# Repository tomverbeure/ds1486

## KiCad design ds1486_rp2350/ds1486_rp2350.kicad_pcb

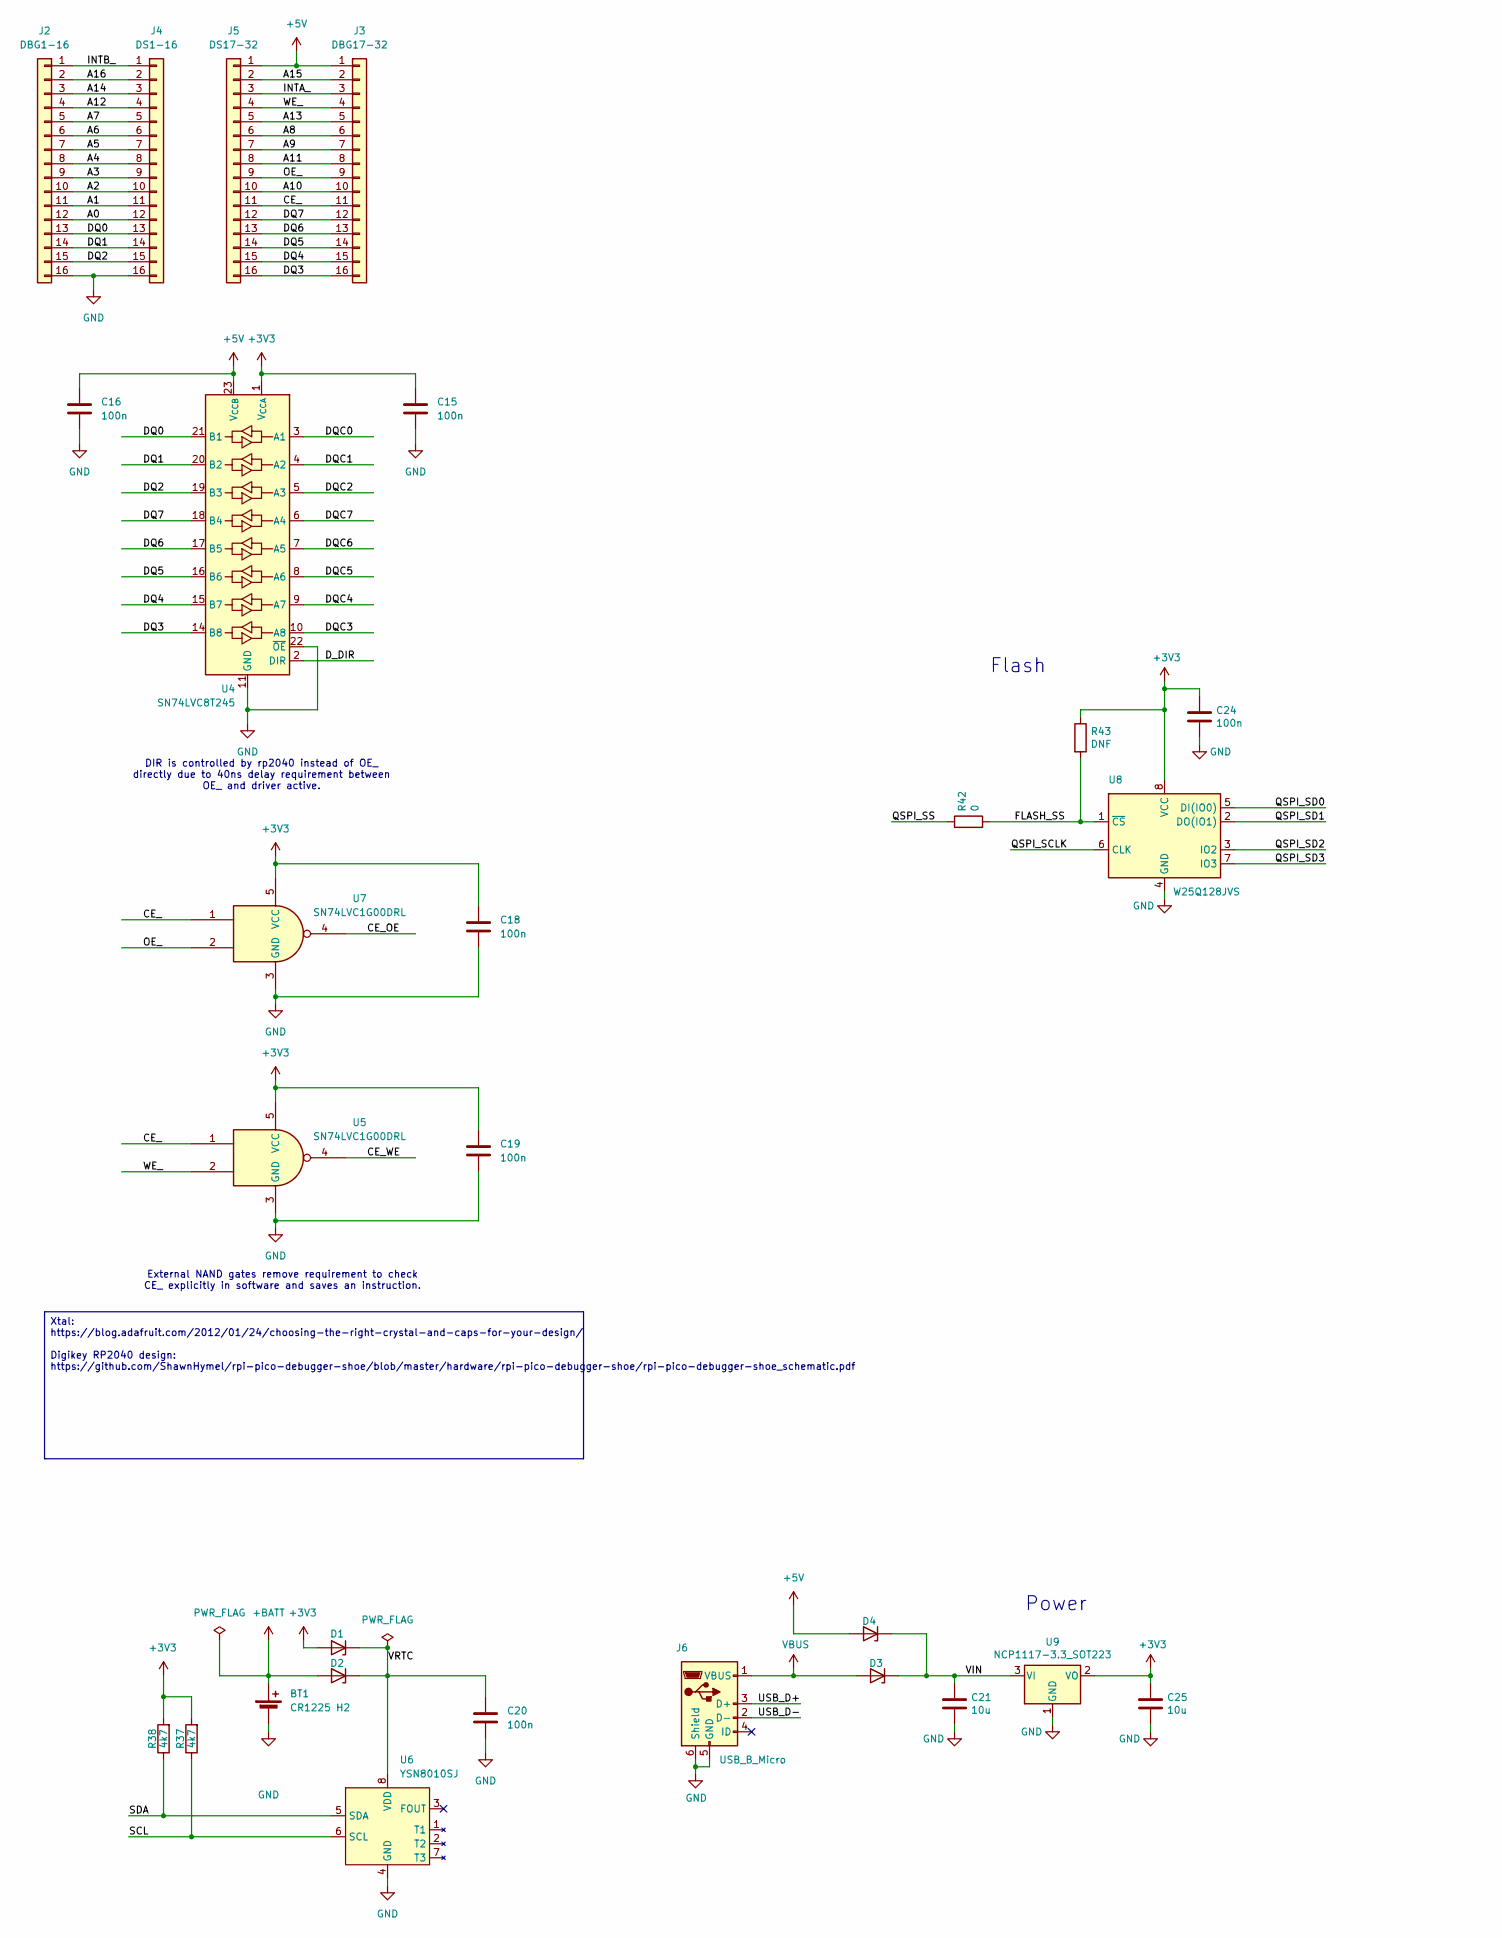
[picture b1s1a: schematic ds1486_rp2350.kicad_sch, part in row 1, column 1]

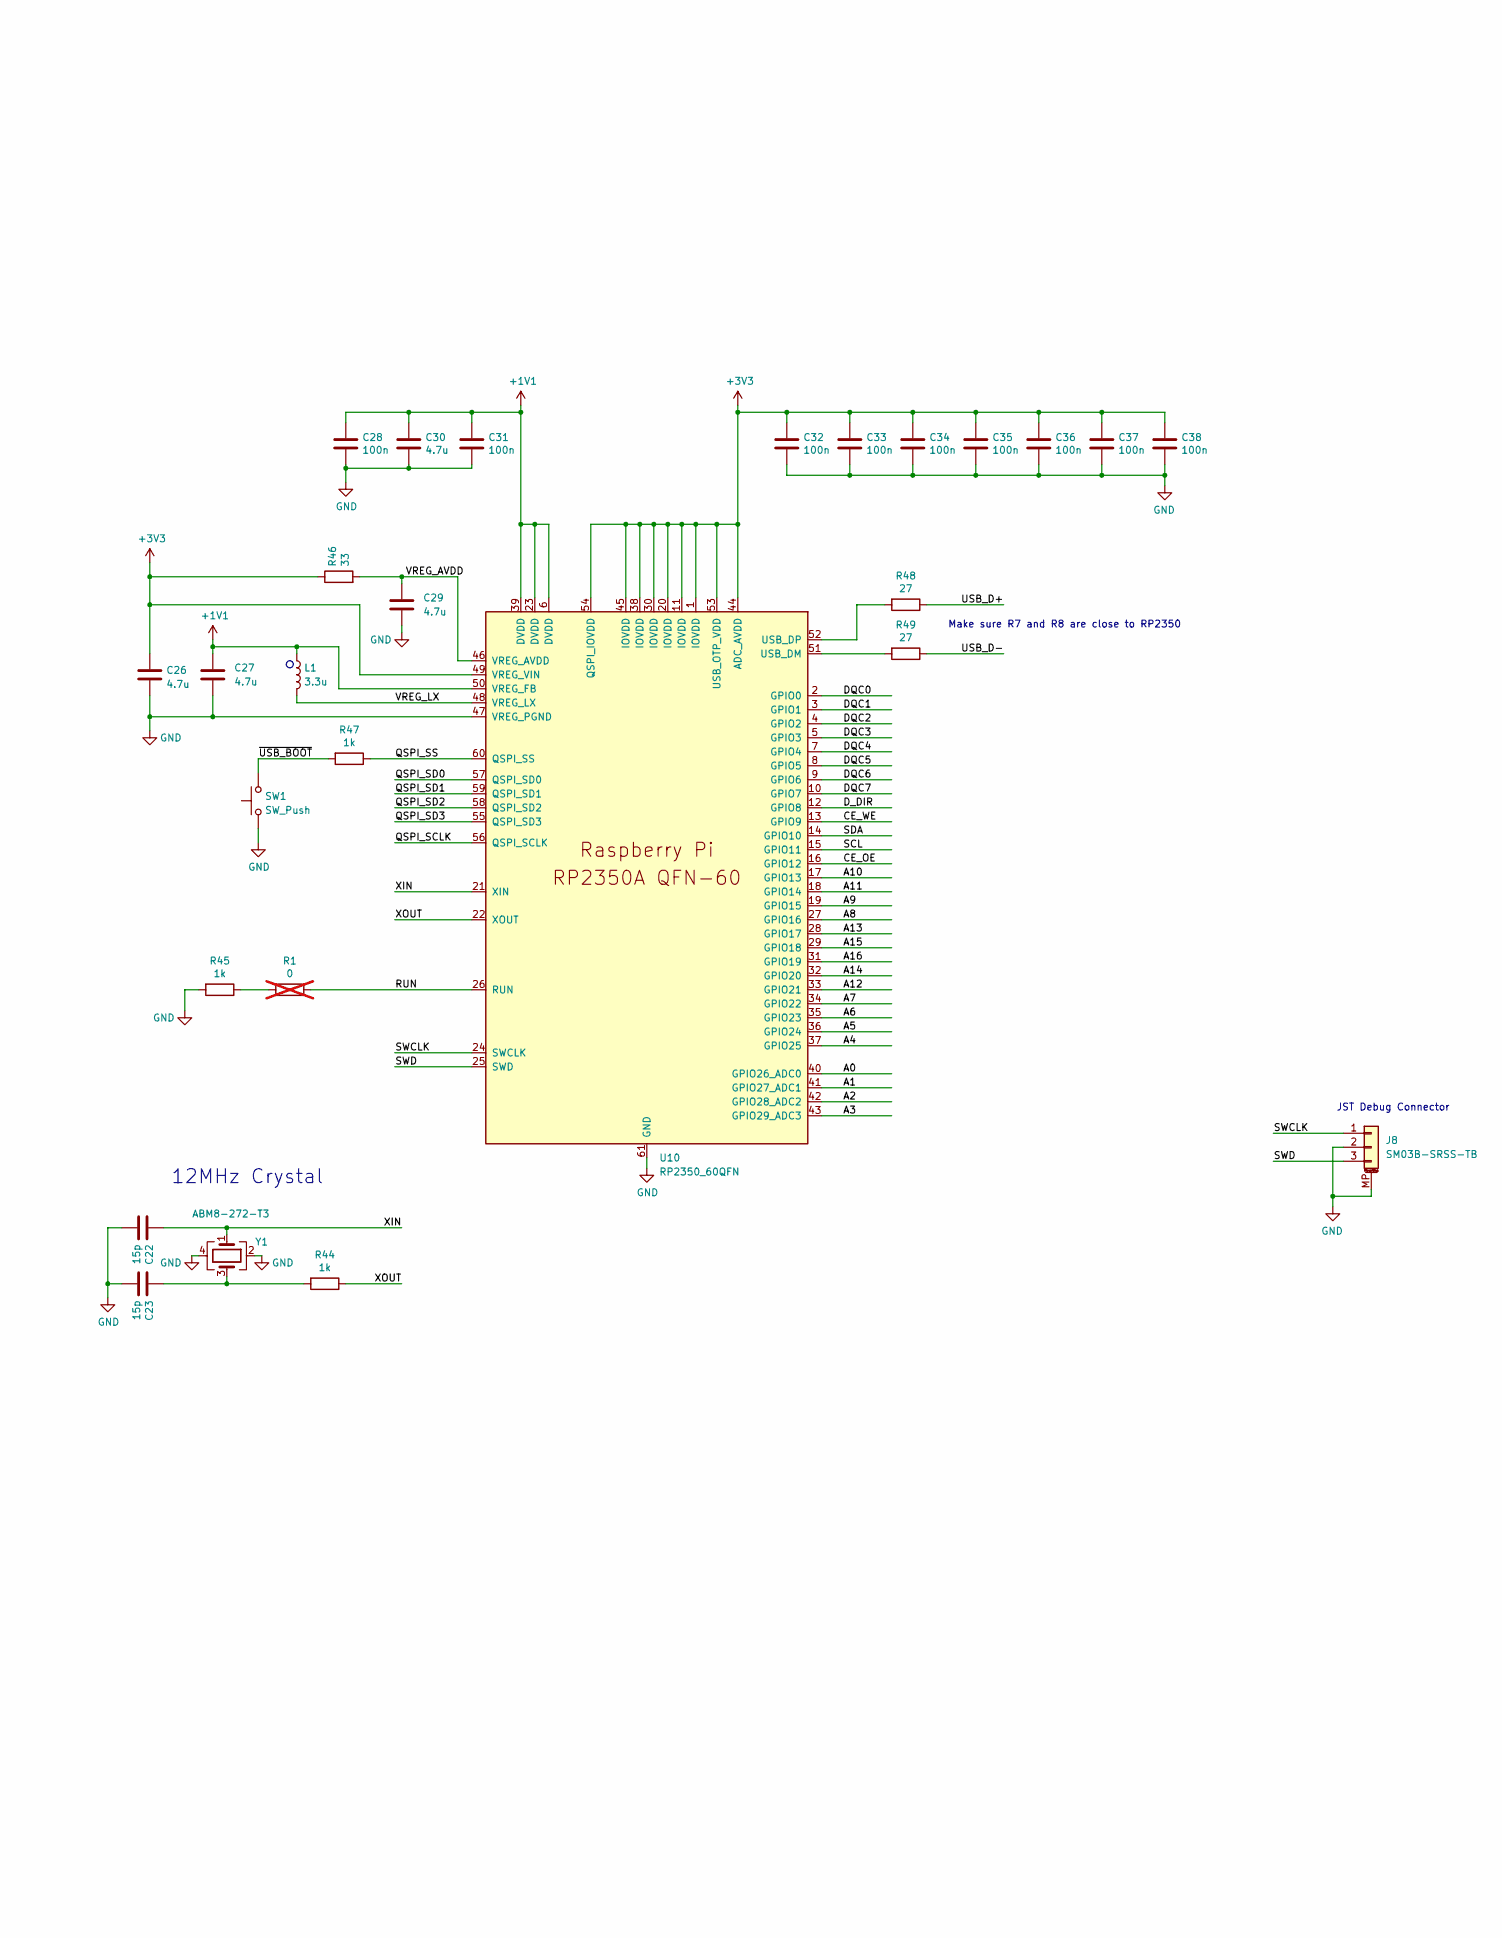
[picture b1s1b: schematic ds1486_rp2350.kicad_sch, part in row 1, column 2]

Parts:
BT1: CR1225 H2; CR1225_H2
C15, C16, C20: 100n; C_0603_1608Metric
C18, C19, C24, C28, C31, C32, C33, C34, C35, C36, C37, C38: 100n; C_0402_1005Metric
C21, C25: 10u; C_0805_2012Metric
C22, C23: 15p; C_0402_1005Metric
C26, C27: 4.7u; C_0402_1005Metric_small_pads
C29, C30: 4.7u; C_0402_1005Metric
D1, D2, D3, D4: BZT52C6V8-7-F; D_SOD-123F
J2: DBG1-16; PinHeader_1x16_P2.54mm_Vertical
J3: DBG17-32; PinHeader_1x16_P2.54mm_Vertical
J4: DS1-16; PinHeader_1x16_P2.54mm_Vertical_DIP_Diameter_Flipside
J5: DS17-32; PinHeader_1x16_P2.54mm_Vertical_DIP_Diameter_Flipside
J6: USB_B_Micro; USB_Micro-B_Amphenol_10103594-0001LF_Horizontal
J8: SM03B-SRSS-TB; JST_SH_SM03B-SRSS-TB_1x03-1MP_P1.00mm_Horizontal
L1: 3.3u; L_pol_2016
R1: 0; R_0402_1005Metric; not fitted
R37, R38: 4k7; R_0402_1005Metric
R42: 0; R_0402_1005Metric
R43: DNF; R_0402_1005Metric
R44, R45, R47: 1k; R_0402_1005Metric
R46: 33; R_0402_1005Metric
R48, R49: 27; R_0402_1005Metric
SW1: SW_Push; SW_Push_1P1T_NO_Vertical_Wuerth_434133025816
U4: SN74LVC8T245; SSOP-24_3.9x8.7mm_P0.635mm
U5, U7: SN74LVC1G00DRL; Texas_R-PDSO-N5_DRL-5
U6: YSN8010SJ; SOP-8_3.9x4.9mm_P1.27mm
U8: W25Q128JVS; SOIC-8_5.23x5.23mm_P1.27mm
U9: NCP1117-3.3_SOT223; SOT-223-3_TabPin2
U10: RP2350_60QFN; QFN-60-1EP_7x7mm_P0.4mm_EP3.4x3.4mm
Y1: ABM8-272-T3; Crystal_SMD_3225-4Pin_3.2x2.5mm

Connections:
+1V1: C27.1, C28.1, C30.1, C31.1, L1.1, U10.6 (DVDD), U10.23 (DVDD), U10.39 (DVDD), U10.50 (VREG_FB)
+3V3: C15.1, C18.1, C19.1, C24.1, C25.1, C26.1, C32.1, C33.1, C34.1, C35.1, C36.1, C37.1, C38.1, D1.2 (A), R37.2, R38.2, R43.1, R46.1, U4.1 (V_{CCA}), U5.5 (VCC), U7.5 (VCC), U8.8 (VCC), U9.2 (VO), U10.1 (IOVDD), U10.11 (IOVDD), U10.20 (IOVDD), U10.30 (IOVDD), U10.38 (IOVDD), U10.44 (ADC_AVDD), U10.45 (IOVDD), U10.49 (VREG_VIN), U10.53 (USB_OTP_VDD), U10.54 (QSPI_IOVDD)
+5V: C16.1, D4.2 (A), J3.1, J5.1, U4.23 (V_{CCB}), U4.24 (V_{CCB})
+BATT: BT1.1 (+), D2.2 (A)
/A0: J2.12, J4.12, U10.40 (GPIO26_ADC0)
/A1: J2.11, J4.11, U10.41 (GPIO27_ADC1)
/A2: J2.10, J4.10, U10.42 (GPIO28_ADC2)
/A3: J2.9, J4.9, U10.43 (GPIO29_ADC3)
/A4: J2.8, J4.8, U10.37 (GPIO25)
/A5: J2.7, J4.7, U10.36 (GPIO24)
/A6: J2.6, J4.6, U10.35 (GPIO23)
/A7: J2.5, J4.5, U10.34 (GPIO22)
/A8: J3.6, J5.6, U10.27 (GPIO16)
/A9: J3.7, J5.7, U10.19 (GPIO15)
/A10: J3.10, J5.10, U10.17 (GPIO13)
/A11: J3.8, J5.8, U10.18 (GPIO14)
/A12: J2.4, J4.4, U10.33 (GPIO21)
/A13: J3.5, J5.5, U10.28 (GPIO17)
/A14: J2.3, J4.3, U10.32 (GPIO20)
/A15: J3.2, J5.2, U10.29 (GPIO18)
/A16: J2.2, J4.2, U10.31 (GPIO19)
/CE_: J3.11, J5.11, U5.1, U7.1
/CE_OE: U7.4, U10.16 (GPIO12)
/CE_WE: U5.4, U10.13 (GPIO9)
/DQ0: J2.13, J4.13, U4.21 (B1)
/DQ1: J2.14, J4.14, U4.20 (B2)
/DQ2: J2.15, J4.15, U4.19 (B3)
/DQ3: J3.16, J5.16, U4.14 (B8)
/DQ4: J3.15, J5.15, U4.15 (B7)
/DQ5: J3.14, J5.14, U4.16 (B6)
/DQ6: J3.13, J5.13, U4.17 (B5)
/DQ7: J3.12, J5.12, U4.18 (B4)
/DQC0: U4.3 (A1), U10.2 (GPIO0)
/DQC1: U4.4 (A2), U10.3 (GPIO1)
/DQC2: U4.5 (A3), U10.4 (GPIO2)
/DQC3: U4.10 (A8), U10.5 (GPIO3)
/DQC4: U4.9 (A7), U10.7 (GPIO4)
/DQC5: U4.8 (A6), U10.8 (GPIO5)
/DQC6: U4.7 (A5), U10.9 (GPIO6)
/DQC7: U4.6 (A4), U10.10 (GPIO7)
/D_DIR: U4.2 (DIR), U10.12 (GPIO8)
/FLASH_SS: R42.2, R43.2, U8.1 (~CS)
/INTA_: J3.3, J5.3
/INTB_: J2.1, J4.1
/OE_: J3.9, J5.9, U7.2
/QSPI_SCLK: U8.6 (CLK), U10.56 (QSPI_SCLK)
/QSPI_SD0: U8.5 (DI(IO0)), U10.57 (QSPI_SD0)
/QSPI_SD1: U8.2 (DO(IO1)), U10.59 (QSPI_SD1)
/QSPI_SD2: U8.3 (IO2), U10.58 (QSPI_SD2)
/QSPI_SD3: U8.7 (IO3), U10.55 (QSPI_SD3)
/QSPI_SS: R42.1, R47.1, U10.60 (QSPI_SS)
/RUN: R1.1, U10.26 (RUN)
/SCL: R37.1, U6.6 (SCL), U10.15 (GPIO11)
/SDA: R38.1, U6.5 (SDA), U10.14 (GPIO10)
/SWCLK: J8.1, U10.24 (SWCLK)
/SWD: J8.3, U10.25 (SWD)
/USB_D+: J6.3 (D+), R48.1
/USB_D-: J6.2 (D-), R49.1
/VIN: C21.1, D3.1 (K), D4.1 (K), U9.3 (VI)
/VREG_AVDD: C29.1, R46.2, U10.46 (VREG_AVDD)
/VREG_LX: L1.2, U10.48 (VREG_LX)
/VRTC: C20.1, D1.1 (K), D2.1 (K), U6.8 (VDD)
/WE_: J3.4, J5.4, U5.2
/XIN: C22.1, U10.21 (XIN), Y1.1
/XOUT: R44.1, U10.22 (XOUT)
/~USB_BOOT: R47.2, SW1.2
GND: BT1.2 (-), C15.2, C16.2, C18.2, C19.2, C20.2, C21.2, C22.2, C23.2, C24.2, C25.2, C26.2, C27.2, C28.2, C29.2, C30.2, C31.2, C32.2, C33.2, C34.2, C35.2, C36.2, C37.2, C38.2, J2.16, J4.16, J6.5 (GND), J6.6 (Shield), J8.2, J8.MP (MountPin), R45.2, SW1.1, U4.11 (GND), U4.12 (GND), U4.13 (GND), U4.22 (~OE), U5.3 (GND), U6.4 (GND), U7.3 (GND), U8.4 (GND), U9.1 (GND), U10.47 (VREG_PGND), U10.61 (GND), Y1.2, Y1.4
unnamed: C23.1, R44.2, Y1.3
unnamed: R1.2, R45.1
unnamed: R49.2, U10.51 (USB_DM)
unnamed: R48.2, U10.52 (USB_DP)
VBUS: D3.2 (A), J6.1 (VBUS)

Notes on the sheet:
Flash
DIR is controlled by rp2040 instead of OE_ directly due to 40ns delay requirement between OE_ and driver active.
External NAND gates remove requirement to check CE_ explicitly in software and saves an instruction.
12MHz Crystal
Make sure R7 and R8 are close to RP2350
Power
JST Debug Connector
Xtal: https://blog.adafruit.com/2012/01/24/choosing-the-right-crystal-and-caps-for-your-design/ Digikey RP2040 design: https://github.com/ShawnHymel/rpi-pico-debugger-shoe/blob/master/hardware/rpi-pico-debugger-shoe/rpi-pico-debugger-shoe_schematic.pdf

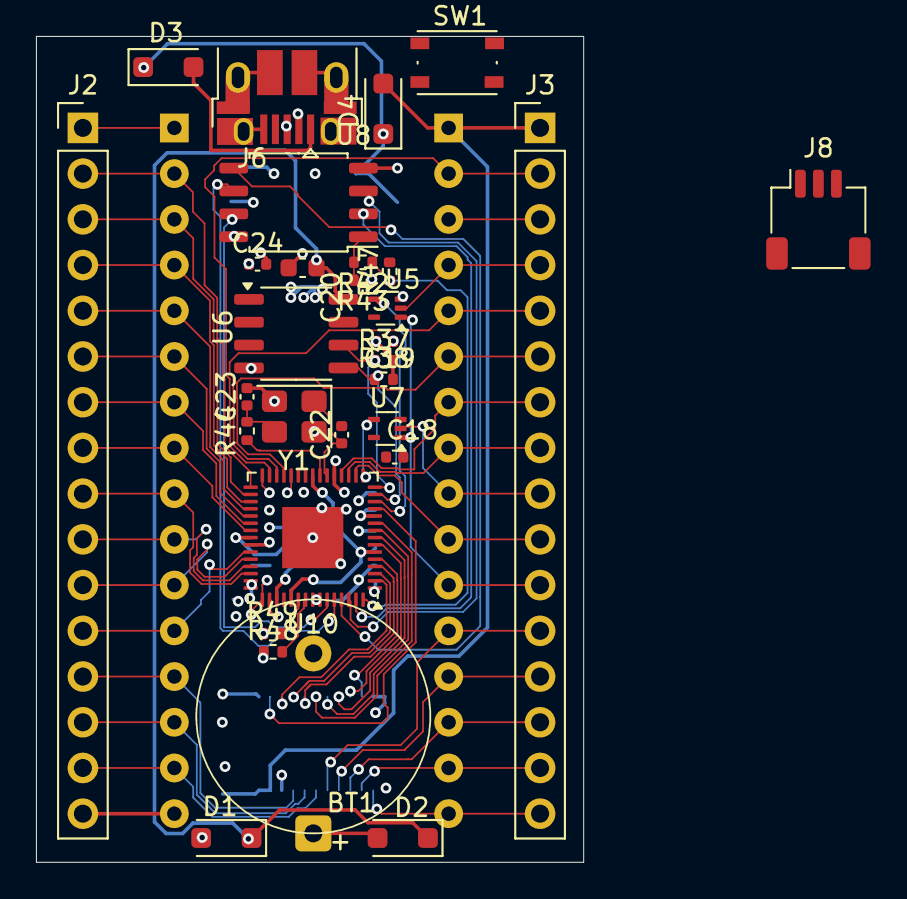
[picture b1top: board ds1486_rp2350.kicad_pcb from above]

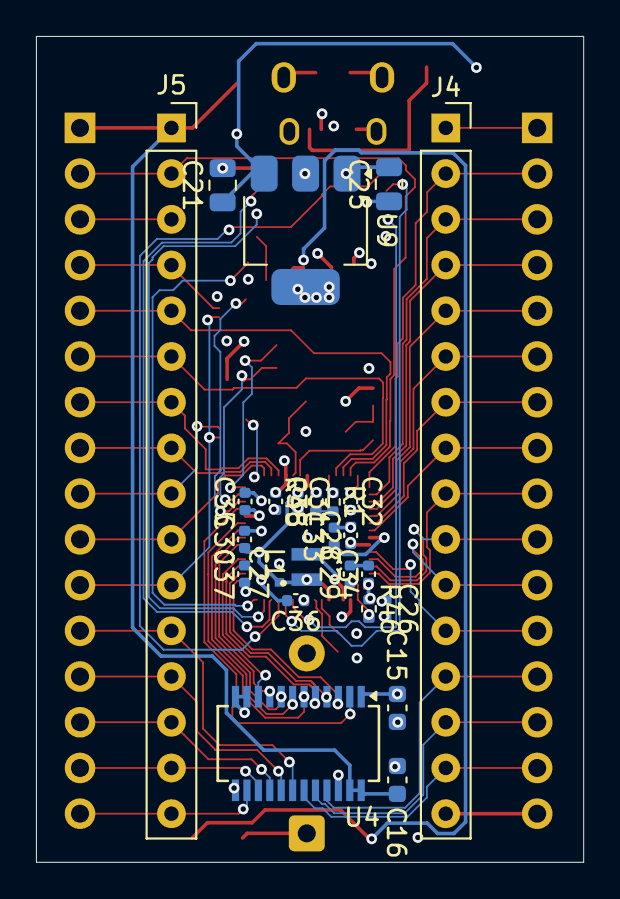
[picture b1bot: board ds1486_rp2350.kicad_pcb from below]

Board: 4 copper layers, 30.4 x 45.9 mm, 55 parts (23 on the bottom side), 72 nets.

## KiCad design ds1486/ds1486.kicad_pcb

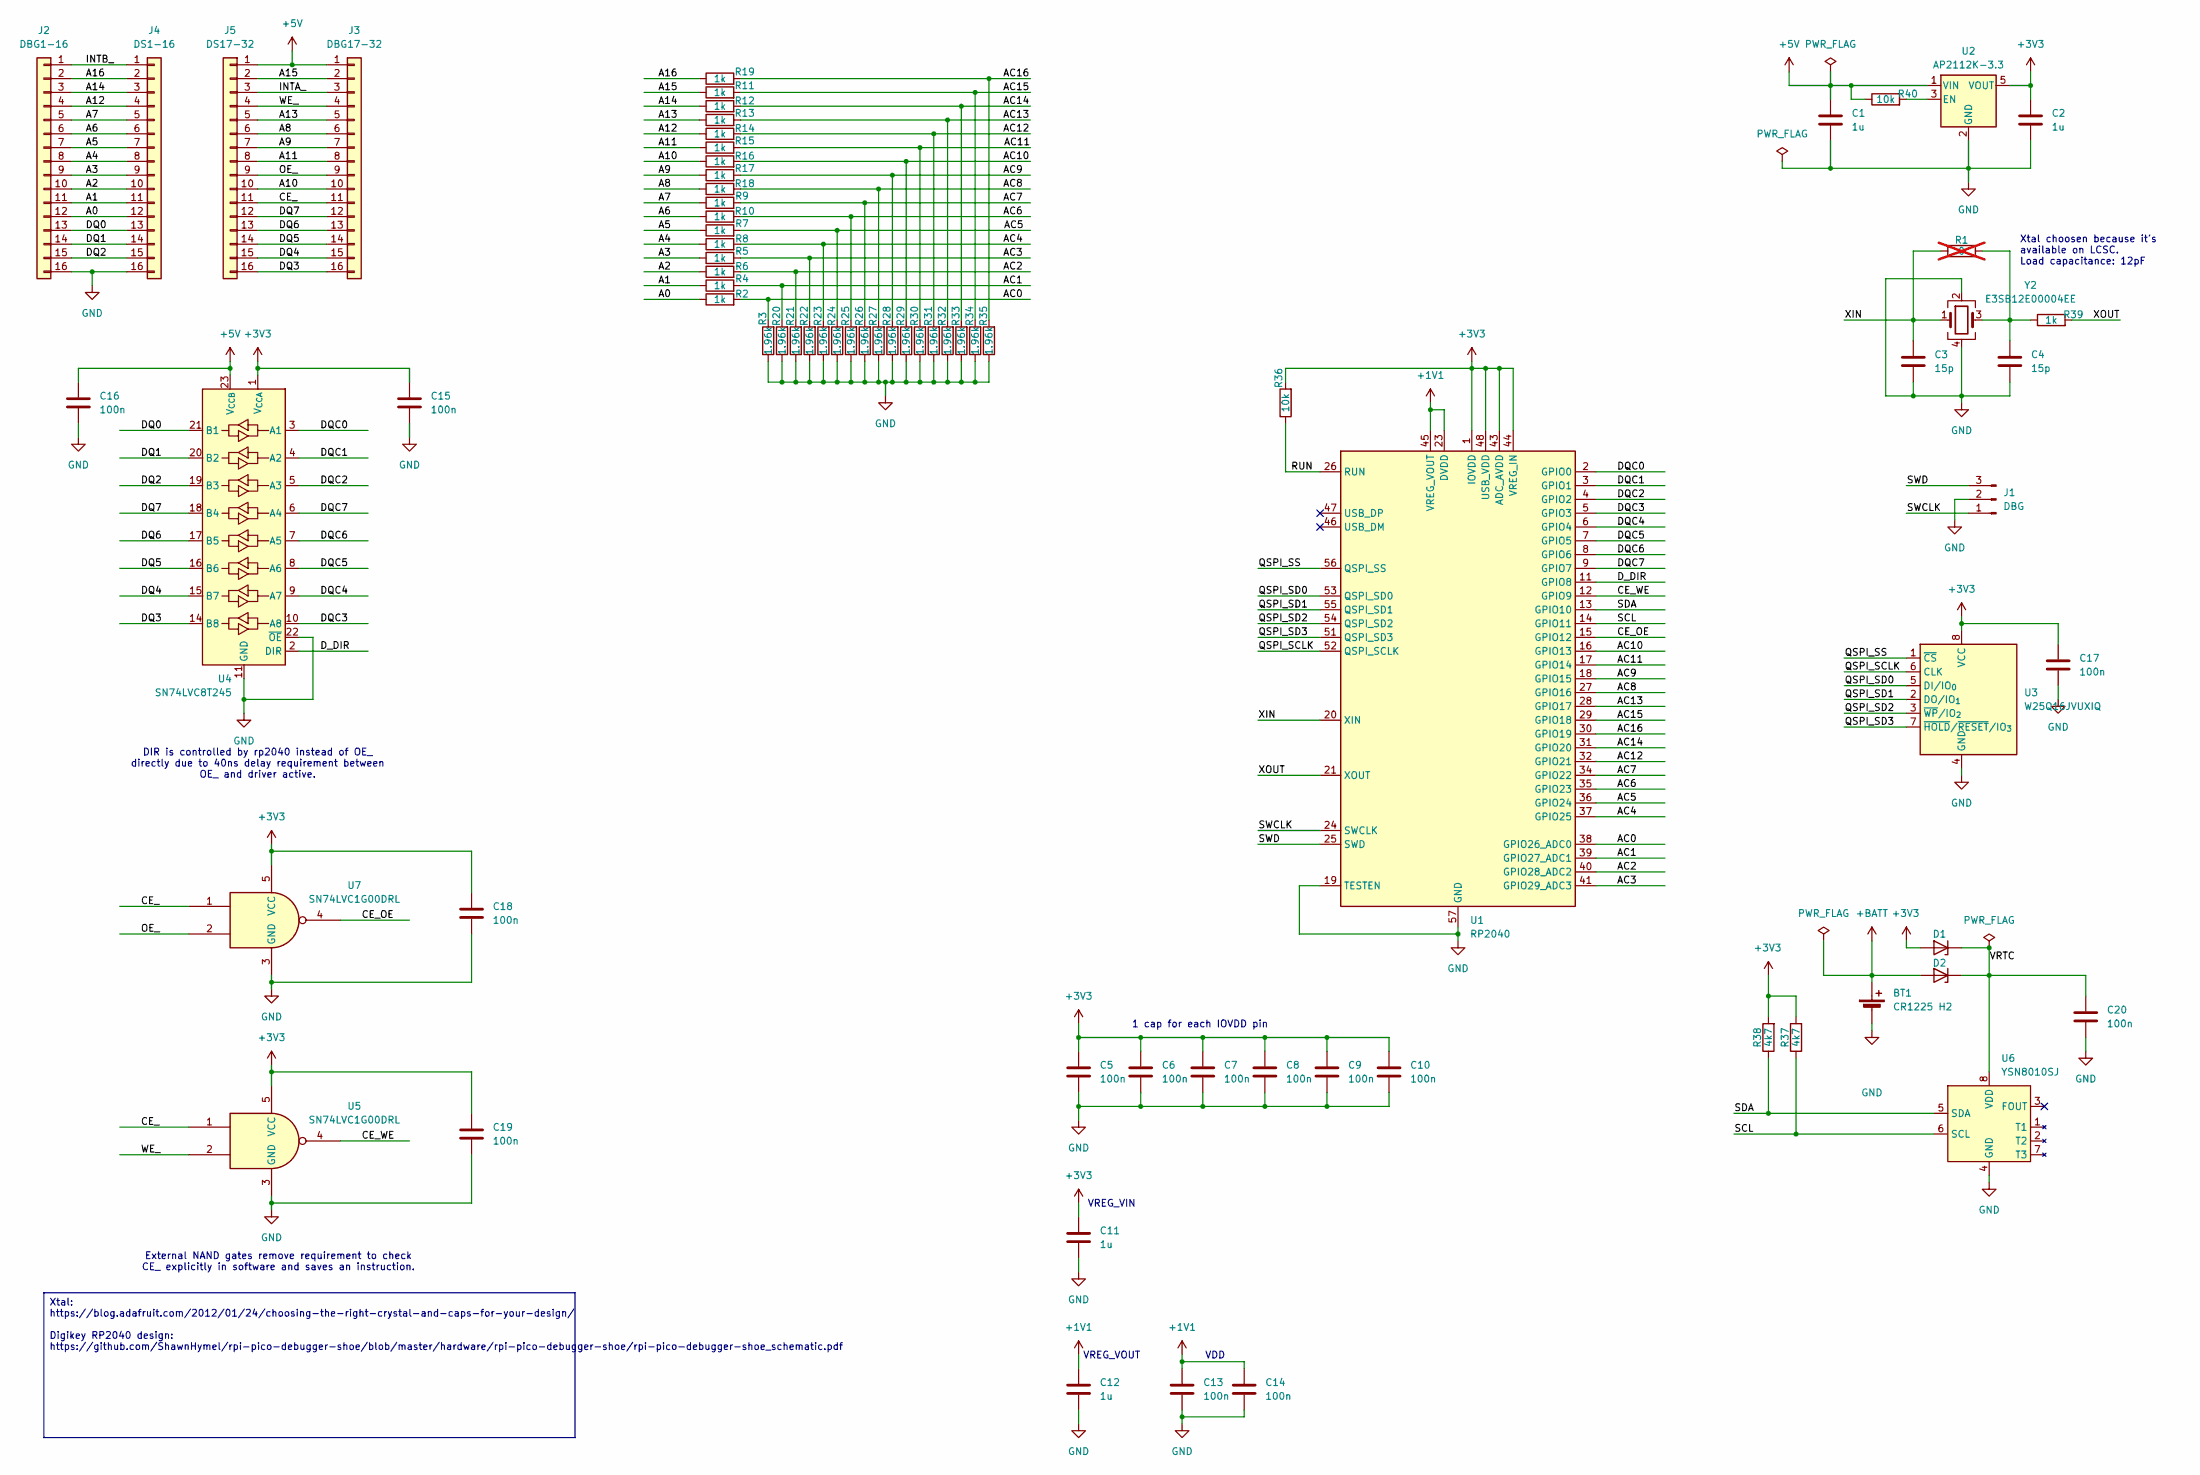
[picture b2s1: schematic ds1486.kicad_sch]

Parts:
BT1: CR1225 H2; CR1225_H2
C1, C2, C11, C12: 1u; C_0603_1608Metric
C3, C4: 15p; C_0603_1608Metric
C5, C6, C7, C8, C9, C10, C13, C14, C15, C16, C17, C20: 100n; C_0603_1608Metric
C18, C19: 100n; C_0402_1005Metric
D1, D2: BZT52C6V8-7-F; D_SOD-123F
J1: DBG; PinHeader_1x03_P2.54mm_Vertical
J2: DBG1-16; PinHeader_1x16_P2.54mm_Vertical
J3: DBG17-32; PinHeader_1x16_P2.54mm_Vertical
J4: DS1-16; PinHeader_1x16_P2.54mm_Vertical_DIP_Diameter_Flipside
J5: DS17-32; PinHeader_1x16_P2.54mm_Vertical_DIP_Diameter_Flipside
R1: 0; R_0603_1608Metric; not fitted
R2, R4, R5, R6, R7, R8, R9, R10, R11, R12, R13, R14, R15, R16, R17, R18, R19, R39: 1k; R_0402_1005Metric
R3, R20, R21, R22, R23, R24, R25, R26, R27, R28, R29, R30, R31, R32, R33, R34, R35: 1.96k; R_0402_1005Metric
R36, R40: 10k; R_0402_1005Metric
R37, R38: 4k7; R_0603_1608Metric
U1: RP2040; QFN-56-1EP_7x7mm_P0.4mm_EP3.2x3.2mm
U2: AP2112K-3.3; SOT-23-5
U3: W25Q16JVUXIQ; Winbond_USON-8-1EP_3x2mm_P0.5mm_EP0.2x1.6mm
U4: SN74LVC8T245; SSOP-24_3.9x8.7mm_P0.635mm
U5, U7: SN74LVC1G00DRL; Texas_R-PDSO-N5_DRL-5
U6: YSN8010SJ; SOP-8_3.9x4.9mm_P1.27mm
Y2: E3SB12E00004EE; Crystal_SMD_3225-4Pin_3.2x2.5mm

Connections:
+1V1: C12.1, C13.1, C14.1, U1.23 (DVDD), U1.45 (VREG_VOUT), U1.50 (DVDD)
+3V3: C2.1, C5.1, C6.1, C7.1, C8.1, C9.1, C10.1, C11.1, C15.1, C17.1, C18.1, C19.1, D1.2 (A), R36.2, R37.2, R38.2, U1.1 (IOVDD), U1.10 (IOVDD), U1.22 (IOVDD), U1.33 (IOVDD), U1.42 (IOVDD), U1.43 (ADC_AVDD), U1.44 (VREG_IN), U1.48 (USB_VDD), U1.49 (IOVDD), U2.5 (VOUT), U3.8 (VCC), U4.1 (V_{CCA}), U5.5 (VCC), U7.5 (VCC)
+5V: C1.1, C16.1, J3.1, J5.1, R40.1, U2.1 (VIN), U4.23 (V_{CCB}), U4.24 (V_{CCB})
+BATT: BT1.1 (+), D2.2 (A)
/A0: J2.12, J4.12, R2.1
/A1: J2.11, J4.11, R4.1
/A2: J2.10, J4.10, R6.1
/A3: J2.9, J4.9, R5.1
/A4: J2.8, J4.8, R8.1
/A5: J2.7, J4.7, R7.1
/A6: J2.6, J4.6, R10.1
/A7: J2.5, J4.5, R9.1
/A8: J3.6, J5.6, R18.1
/A9: J3.7, J5.7, R17.1
/A10: J3.10, J5.10, R16.1
/A11: J3.8, J5.8, R15.1
/A12: J2.4, J4.4, R14.1
/A13: J3.5, J5.5, R13.1
/A14: J2.3, J4.3, R12.1
/A15: J3.2, J5.2, R11.1
/A16: J2.2, J4.2, R19.1
/AC0: R2.2, R3.2, U1.38 (GPIO26_ADC0)
/AC1: R4.2, R20.2, U1.39 (GPIO27_ADC1)
/AC2: R6.2, R21.2, U1.40 (GPIO28_ADC2)
/AC3: R5.2, R22.2, U1.41 (GPIO29_ADC3)
/AC4: R8.2, R23.2, U1.37 (GPIO25)
/AC5: R7.2, R24.2, U1.36 (GPIO24)
/AC6: R10.2, R25.2, U1.35 (GPIO23)
/AC7: R9.2, R26.2, U1.34 (GPIO22)
/AC8: R18.2, R27.2, U1.27 (GPIO16)
/AC9: R17.2, R28.2, U1.18 (GPIO15)
/AC10: R16.2, R29.2, U1.16 (GPIO13)
/AC11: R15.2, R30.2, U1.17 (GPIO14)
/AC12: R14.2, R31.2, U1.32 (GPIO21)
/AC13: R13.2, R32.2, U1.28 (GPIO17)
/AC14: R12.2, R33.2, U1.31 (GPIO20)
/AC15: R11.2, R34.2, U1.29 (GPIO18)
/AC16: R19.2, R35.2, U1.30 (GPIO19)
/CE_: J3.11, J5.11, U5.1, U7.1
/CE_OE: U1.15 (GPIO12), U7.4
/CE_WE: U1.12 (GPIO9), U5.4
/DQ0: J2.13, J4.13, U4.21 (B1)
/DQ1: J2.14, J4.14, U4.20 (B2)
/DQ2: J2.15, J4.15, U4.19 (B3)
/DQ3: J3.16, J5.16, U4.14 (B8)
/DQ4: J3.15, J5.15, U4.15 (B7)
/DQ5: J3.14, J5.14, U4.16 (B6)
/DQ6: J3.13, J5.13, U4.17 (B5)
/DQ7: J3.12, J5.12, U4.18 (B4)
/DQC0: U1.2 (GPIO0), U4.3 (A1)
/DQC1: U1.3 (GPIO1), U4.4 (A2)
/DQC2: U1.4 (GPIO2), U4.5 (A3)
/DQC3: U1.5 (GPIO3), U4.10 (A8)
/DQC4: U1.6 (GPIO4), U4.9 (A7)
/DQC5: U1.7 (GPIO5), U4.8 (A6)
/DQC6: U1.8 (GPIO6), U4.7 (A5)
/DQC7: U1.9 (GPIO7), U4.6 (A4)
/D_DIR: U1.11 (GPIO8), U4.2 (DIR)
/INTA_: J3.3, J5.3
/INTB_: J2.1, J4.1
/OE_: J3.9, J5.9, U7.2
/QSPI_SCLK: U1.52 (QSPI_SCLK), U3.6 (CLK)
/QSPI_SD0: U1.53 (QSPI_SD0), U3.5 (DI/IO_{0})
/QSPI_SD1: U1.55 (QSPI_SD1), U3.2 (DO/IO_{1})
/QSPI_SD2: U1.54 (QSPI_SD2), U3.3 (~WP/IO_{2})
/QSPI_SD3: U1.51 (QSPI_SD3), U3.7 (~HOLD/~RESET/IO_{3})
/QSPI_SS: U1.56 (QSPI_SS), U3.1 (~CS)
/RUN: R36.1, U1.26 (RUN)
/SCL: R37.1, U1.14 (GPIO11), U6.6 (SCL)
/SDA: R38.1, U1.13 (GPIO10), U6.5 (SDA)
/SWCLK: J1.1, U1.24 (SWCLK)
/SWD: J1.3, U1.25 (SWD)
/VRTC: C20.1, D1.1 (K), D2.1 (K), U6.8 (VDD)
/WE_: J3.4, J5.4, U5.2
/XIN: C3.1, R1.1, U1.20 (XIN), Y2.1
/XOUT: R39.2, U1.21 (XOUT)
GND: BT1.2 (-), C1.2, C2.2, C3.2, C4.2, C5.2, C6.2, C7.2, C8.2, C9.2, C10.2, C11.2, C12.2, C13.2, C14.2, C15.2, C16.2, C17.2, C18.2, C19.2, C20.2, J1.2, J2.16, J4.16, R3.1, R20.1, R21.1, R22.1, R23.1, R24.1, R25.1, R26.1, R27.1, R28.1, R29.1, R30.1, R31.1, R32.1, R33.1, R34.1, R35.1, U1.19 (TESTEN), U1.57 (GND), U2.2 (GND), U3.4 (GND), U4.11 (GND), U4.12 (GND), U4.13 (GND), U4.22 (~OE), U5.3 (GND), U6.4 (GND), U7.3 (GND), Y2.2, Y2.4
unnamed: C4.1, R1.2, R39.1, Y2.3
unnamed: R40.2, U2.3 (EN)

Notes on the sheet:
VDD
VREG_VOUT
DIR is controlled by rp2040 instead of OE_ directly due to 40ns delay requirement between OE_ and driver active.
Xtal choosen because it's available on LCSC. Load capacitance: 12pF
External NAND gates remove requirement to check CE_ explicitly in software and saves an instruction.
1 cap for each IOVDD pin
VREG_VIN
Xtal: https://blog.adafruit.com/2012/01/24/choosing-the-right-crystal-and-caps-for-your-design/ Digikey RP2040 design: https://github.com/ShawnHymel/rpi-pico-debugger-shoe/blob/master/hardware/rpi-pico-debugger-shoe/rpi-pico-debugger-shoe_schematic.pdf

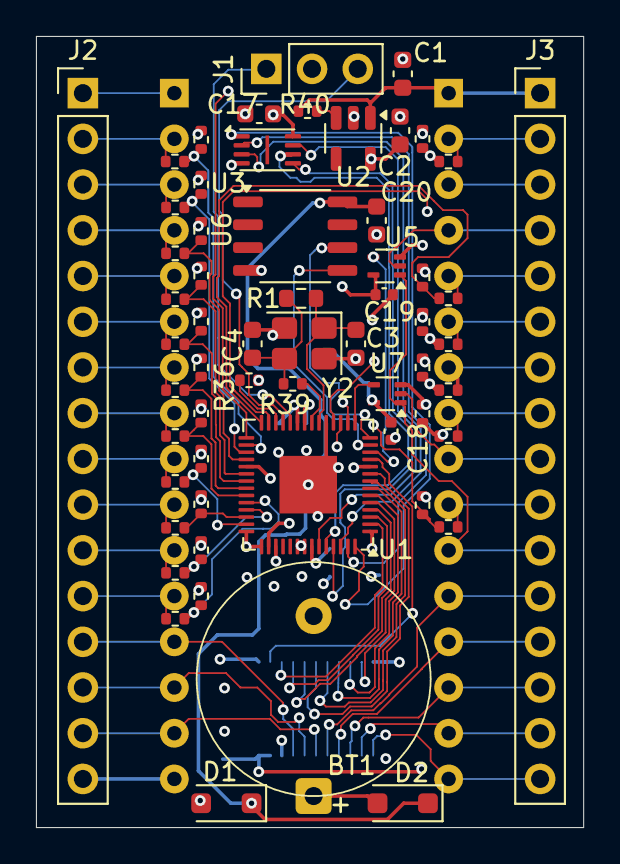
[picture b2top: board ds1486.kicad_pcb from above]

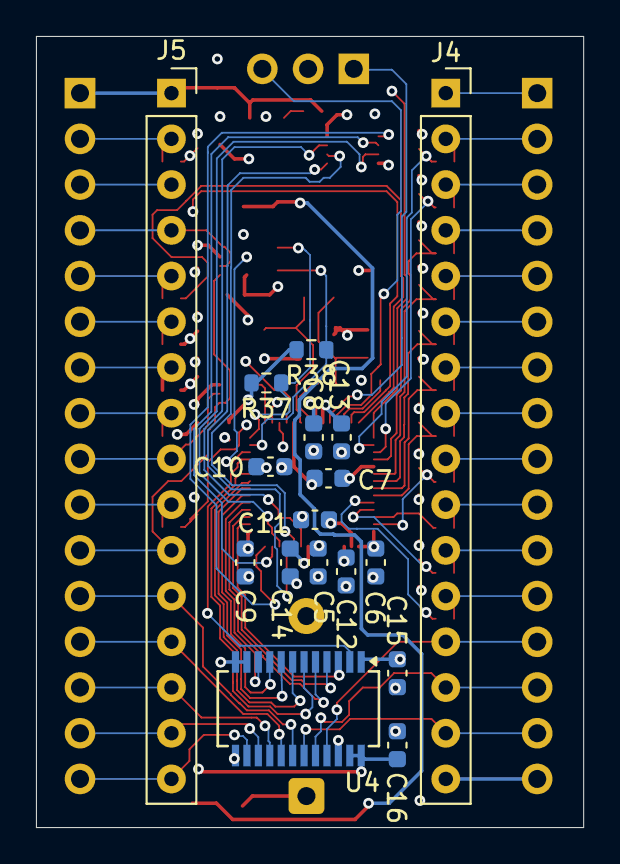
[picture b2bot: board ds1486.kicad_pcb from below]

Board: 4 copper layers, 30.4 x 43.9 mm, 76 parts (15 on the bottom side), 79 nets.

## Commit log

2025-05-11 Start.
2025-05-27 PCB without RTC and battery.
2025-06-06 Add RTC.
2025-06-07 Add battery and narrow pin header.
2025-06-12 Fully routed.
2025-06-23 Add some decoupling caps. Gerbers.
2025-06-24 Move VRTC and SPI flash to front layer.
2025-06-24 Move D_DIR.
2025-06-24 Remove old W25Q16.
2025-09-17 ds1486-rp2350 first version.
